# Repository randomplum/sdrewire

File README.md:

# SDReWire

Modern SD card muxer - allows to mux a SD card between an on-board USB SD card
reader and the device SDReWire is plugged into. This is useful for developing
and testing (embedded) systems which often require SD cards to boot from. It
allows to access the SD card on the target system as well as from the host
system connected via USB without having to touch the SD card.
 
Inspiried by the SDWire.

## Features

- USB-C connector for host system
- High speed signal muxer to mux SD signals
- SDXC/UHS capable design
- USB 3.1 Gen1 card reader (90MB/s+)
- FTDI for SD muxing and auxiliary port
- Auxiliary port featuring:
  - UART
  - 2 GPIO (1x output only)
  - 1.2V/1.8V/3.3V capable

Currenlty SDReWire is still in testing and development phase.

### Details

In case you wonder what exact components are used, here is the gist:

- USB 3.1 Gen1 card reader Genesys Logic GL3224
- TS3DDR4000ZBAR mux IC used for SD signals
- FTDI FT230XQ provides GPIO for mux as well as auxiliary UART and GPIO
- USB2422 USB 2.0 Hub to interface GL3224 and FTDI FT230XQ
  
Designed with KiCad.

## License

Licensed under the CERN-OHL-W (CERN Open Hardware Licence Version 2 - Weakly
Reciprocal, see LICENSE).

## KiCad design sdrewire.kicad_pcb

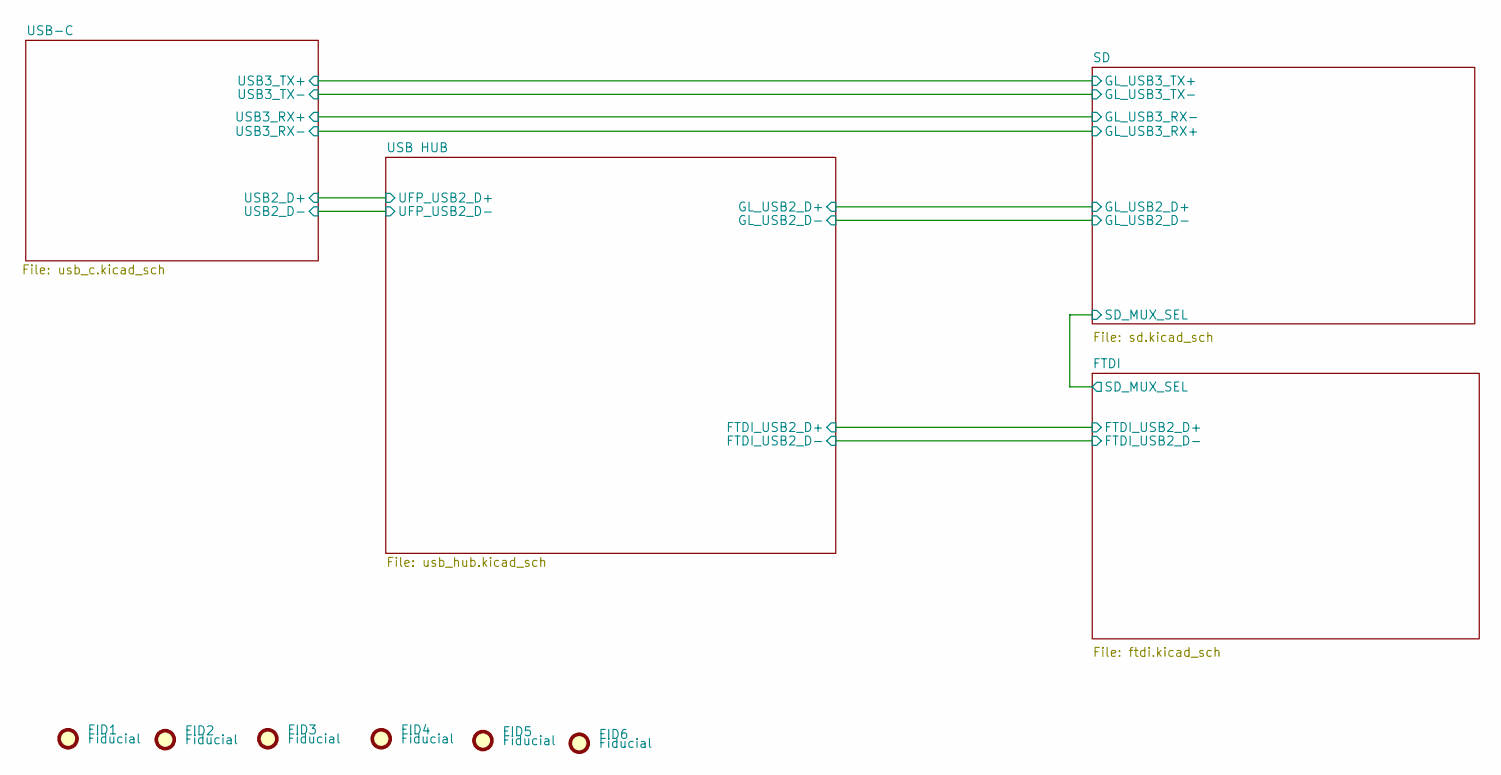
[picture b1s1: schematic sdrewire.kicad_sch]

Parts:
FID1, FID2, FID3, FID4, FID5, FID6: Fiducial; Fiducial_0.5mm_Mask1mm

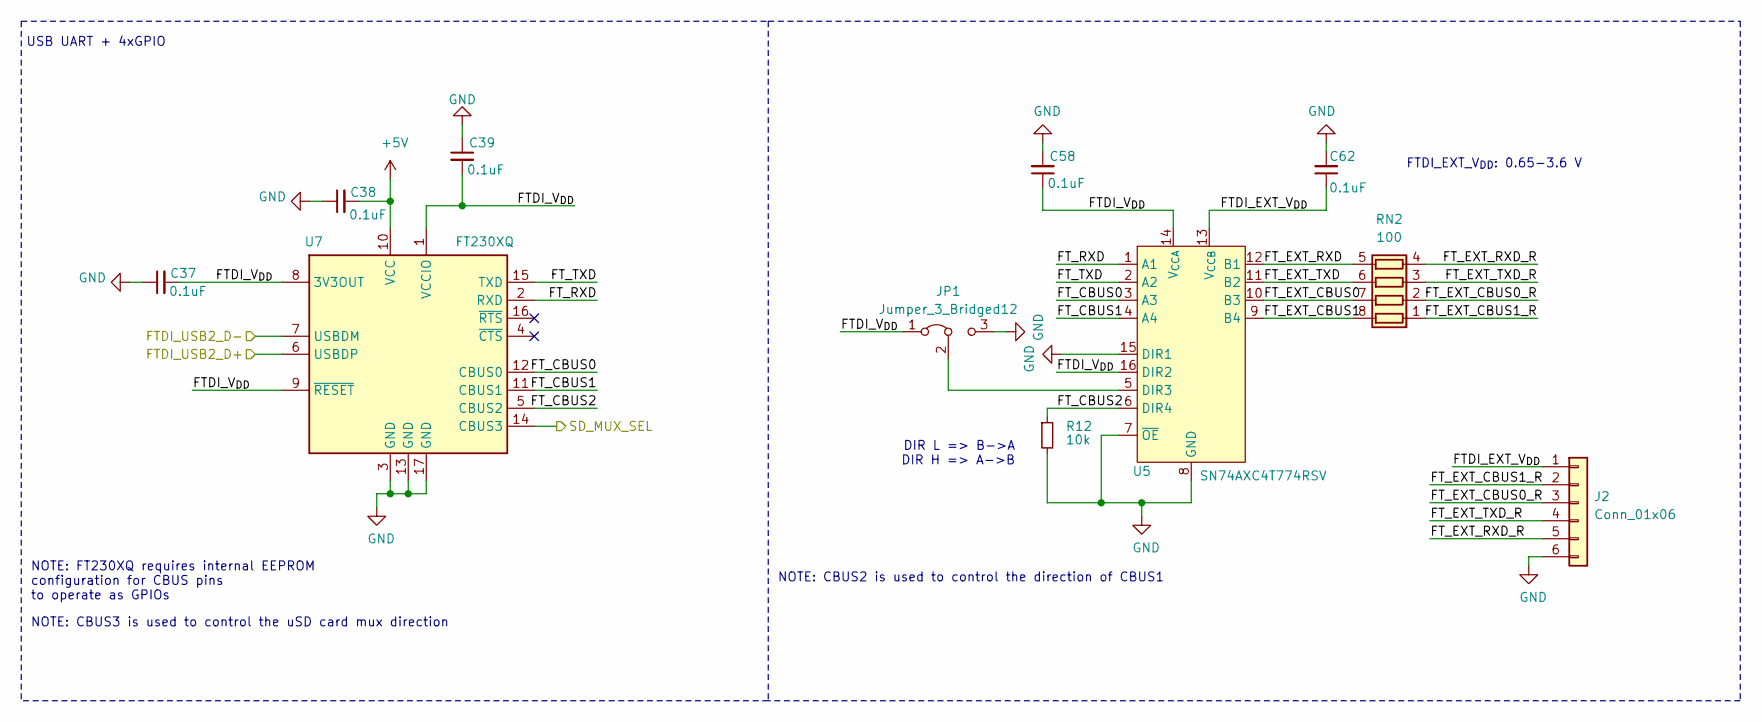
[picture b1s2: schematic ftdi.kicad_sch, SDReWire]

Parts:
C37, C38, C39, C58, C62: 0.1uF; C_0402_1005Metric
J2: Conn_01x06; JST_SH_SM06B-SRSS-TB_1x06-1MP_P1.00mm_Horizontal
JP1: Jumper_3_Bridged12; SolderJumper-3_P1.3mm_Bridged12_RoundedPad1.0x1.5mm_NumberL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
R12: 10k; R_0402_1005Metric
RN2: 100; R_Array_Convex_4x0402
U5: SN74AXC4T774RSV; QFN-16_1.8x2.6_Pitch0.4mm
U7: FT230XQ; QFN-16-1EP_4x4mm_P0.65mm_EP2.1x2.1mm

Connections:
+5V: C38.2, U7.10 (VCC); also elsewhere on the board
/FTDI/FTDI_EXT_V_{DD}: C62.1, J2.1, U5.13 (V_{CCB})
/FTDI/FTDI_USB2_D+: U7.6 (USBDP); also elsewhere on the board
/FTDI/FTDI_USB2_D-: U7.7 (USBDM); also elsewhere on the board
/FTDI/FTDI_V_{DD}: C37.2, C39.2, C58.1, JP1.1 (A), U5.14 (V_{CCA}), U5.16 (DIR2), U7.1 (VCCIO), U7.8 (3V3OUT), U7.9 (~RESET)
/FTDI/FT_CBUS0: U5.3 (A3), U7.12 (CBUS0)
/FTDI/FT_CBUS1: U5.4 (A4), U7.11 (CBUS1)
/FTDI/FT_CBUS2: R12.1, U5.6 (DIR4), U7.5 (CBUS2)
/FTDI/FT_EXT_CBUS0: RN2.7 (R2.2), U5.10 (B3)
/FTDI/FT_EXT_CBUS0_R: J2.3, RN2.2 (R2.1)
/FTDI/FT_EXT_CBUS1: RN2.8 (R1.2), U5.9 (B4)
/FTDI/FT_EXT_CBUS1_R: J2.2, RN2.1 (R1.1)
/FTDI/FT_EXT_RXD: RN2.5 (R4.2), U5.12 (B1)
/FTDI/FT_EXT_RXD_R: J2.5, RN2.4 (R4.1)
/FTDI/FT_EXT_TXD: RN2.6 (R3.2), U5.11 (B2)
/FTDI/FT_EXT_TXD_R: J2.4, RN2.3 (R3.1)
/FTDI/FT_RXD: U5.1 (A1), U7.2 (RXD)
/FTDI/FT_TXD: U5.2 (A2), U7.15 (TXD)
/FTDI/SD_MUX_SEL: U7.14 (CBUS3); also elsewhere on the board
GND: C37.1, C38.1, C39.1, C58.2, C62.2, J2.6, JP1.3 (B), R12.2, U5.7 (~OE), U5.8 (GND), U5.15 (DIR1), U7.3 (GND), U7.13 (GND), U7.17 (GND); also elsewhere on the board
unnamed: JP1.2 (C), U5.5 (DIR3)

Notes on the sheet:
USB UART + 4xGPIO
NOTE: FT230XQ requires internal EEPROM configuration for CBUS pins to operate as GPIOs
NOTE: CBUS3 is used to control the uSD card mux direction
NOTE: CBUS2 is used to control the direction of CBUS1
DIR L => B->A DIR H => A->B
FTDI_EXT_V_{DD}: 0.65-3.6 V

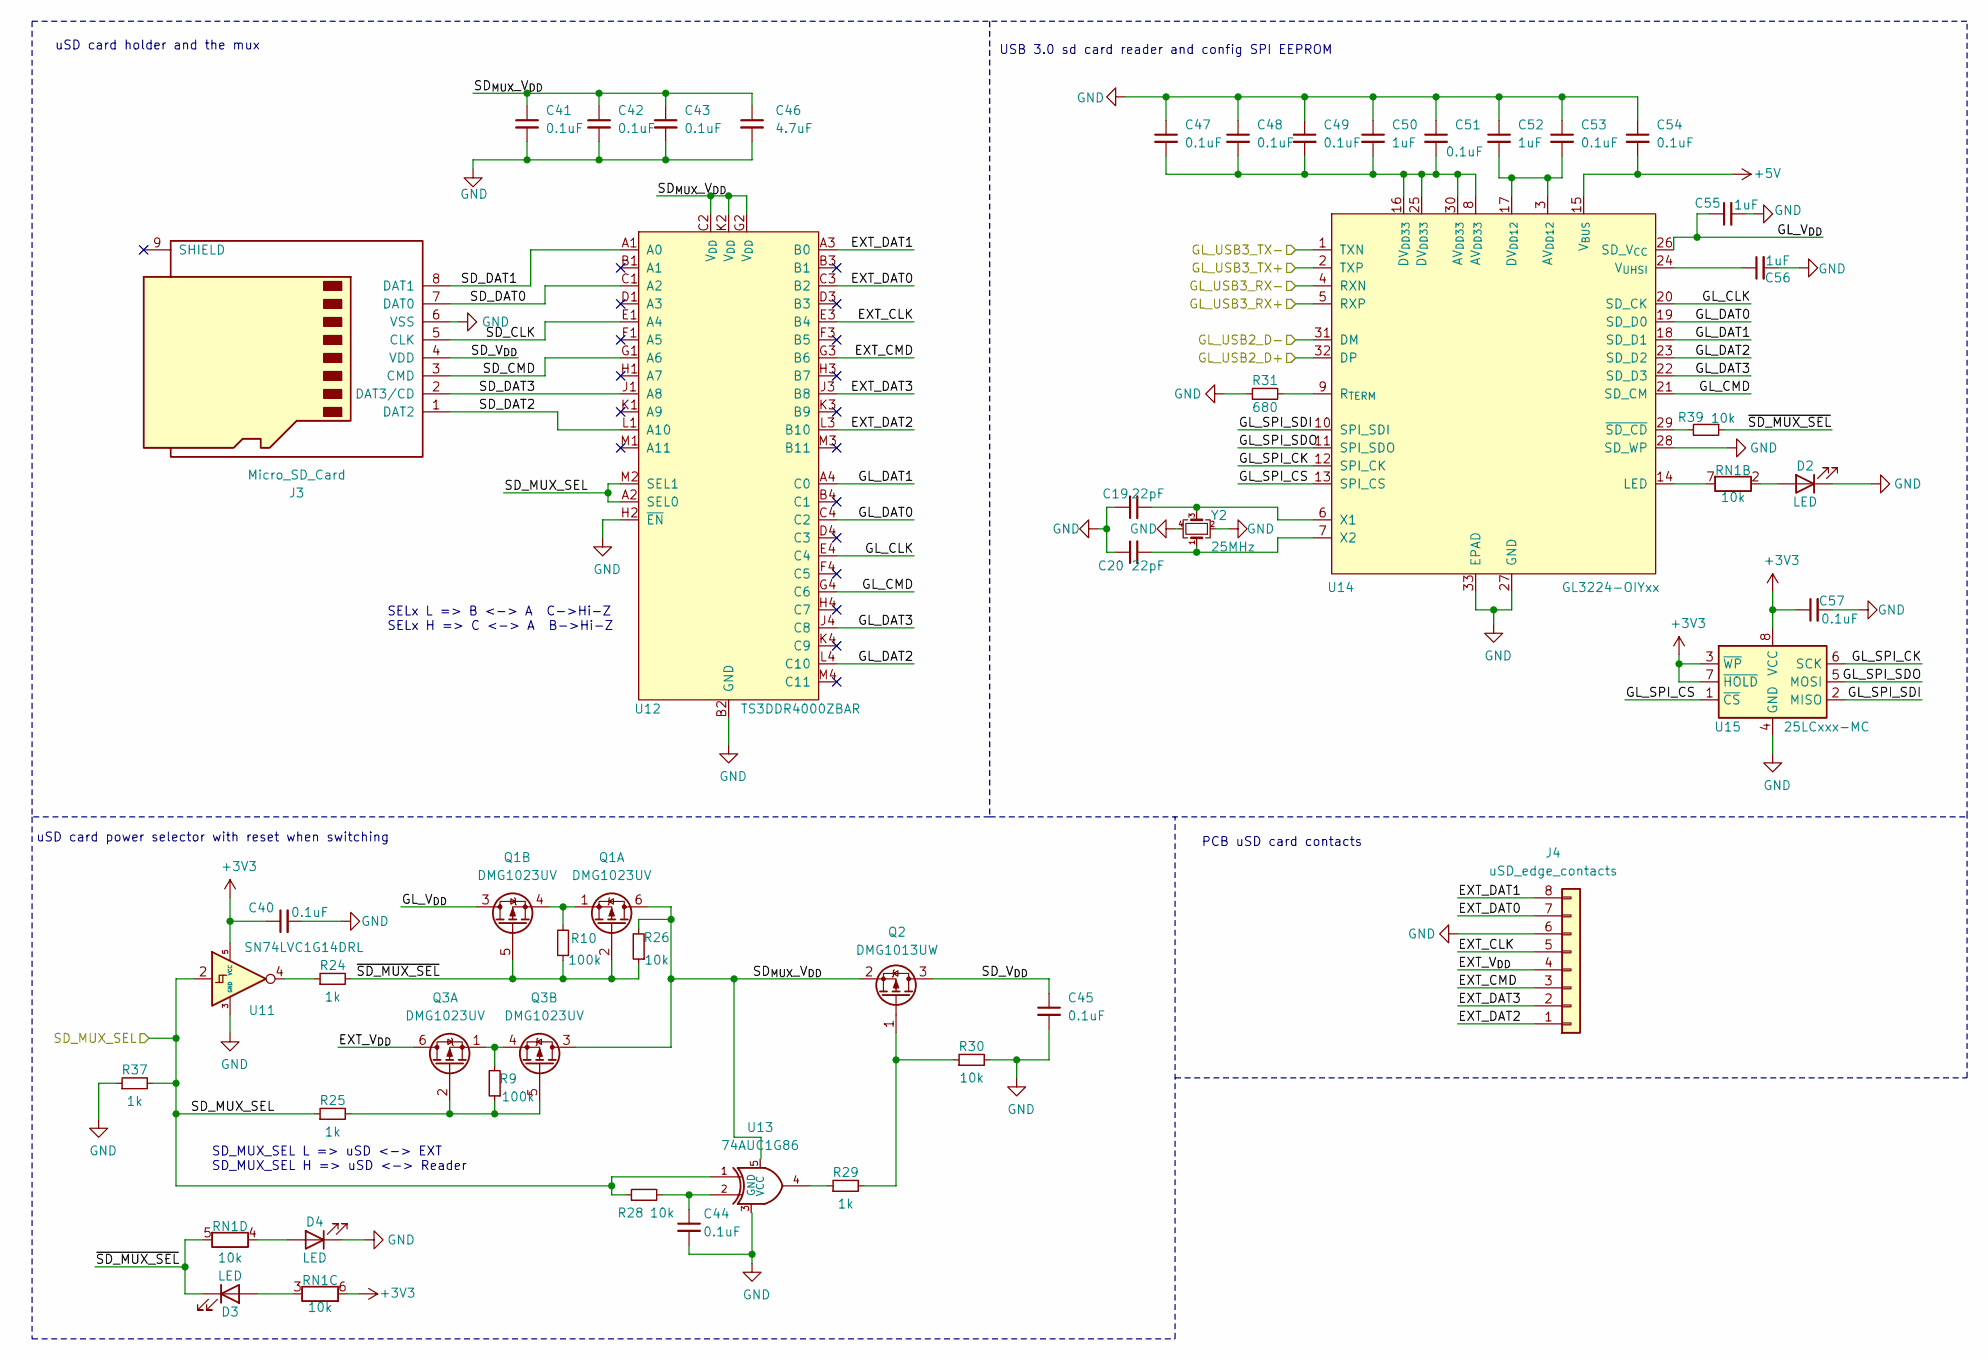
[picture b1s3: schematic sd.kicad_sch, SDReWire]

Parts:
C19, C20: 22pF; C_0402_1005Metric
C40, C41, C42, C43, C44, C45, C47, C48, C49, C51, C53, C54, C57: 0.1uF; C_0402_1005Metric
C46: 4.7uF; C_0402_1005Metric
C50, C52, C55, C56: 1uF; C_0402_1005Metric
D2, D3, D4: LED; LED_0402_1005Metric
J3: Micro_SD_Card; microSD_HC_Wuerth_693072010801
J4: uSD_edge_contacts; uSD_PCB
Q1, Q3: DMG1023UV; SOT-563
Q2: DMG1013UW; SOT-323_SC-70
R9, R10: 100k; R_0402_1005Metric
R24, R25, R29, R37: 1k; R_0402_1005Metric
R26, R28, R30, R39: 10k; R_0402_1005Metric
R31: 680; R_0402_1005Metric
RN1: 10k; R_Array_Convex_4x0402
U11: SN74LVC1G14DRL; SOT-553
U12: TS3DDR4000ZBAR; Texas_NFBGA-48_3.1x8.1mm_Layout4x12_P0.65mm
U13: 74AUC1G86; SOT-353_SC-70-5
U14: GL3224-OIYxx; QFN-32-1EP_5x5mm_P0.5mm_EP3.1x3.1mm
U15: 25LCxxx-MC; DFN-8-1EP_3x2mm_P0.5mm_EP1.75x1.45mm
Y2: 25MHz; Oscillator_SMD_Abracon_ASCO-4Pin_1.6x1.2mm

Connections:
+3V3: C40.1, C57.1, RN1.6 (R3.2), U11.5 (VCC), U15.3 (~WP), U15.7 (~HOLD), U15.8 (VCC); also elsewhere on the board
+5V: C54.2, U14.15 (V_{BUS}); also elsewhere on the board
/FTDI/SD_MUX_SEL: R25.1, R28.1, R37.2, U11.2, U12.A2 (SEL0), U12.M2 (SEL1), U13.1; also elsewhere on the board
/SD/EXT_CLK: J4.5, U12.E3 (B4)
/SD/EXT_CMD: J4.3, U12.G3 (B6)
/SD/EXT_DAT0: J4.7, U12.C3 (B2)
/SD/EXT_DAT1: J4.8, U12.A3 (B0)
/SD/EXT_DAT2: J4.1, U12.L3 (B10)
/SD/EXT_DAT3: J4.2, U12.J3 (B8)
/SD/EXT_V_{DD}: J4.4, Q3.6 (D)
/SD/GL_CLK: U12.E4 (C4), U14.20 (SD_CK)
/SD/GL_CMD: U12.G4 (C6), U14.21 (SD_CM)
/SD/GL_DAT0: U12.C4 (C2), U14.19 (SD_D0)
/SD/GL_DAT1: U12.A4 (C0), U14.18 (SD_D1)
/SD/GL_DAT2: U12.L4 (C10), U14.23 (SD_D2)
/SD/GL_DAT3: U12.J4 (C8), U14.22 (SD_D3)
/SD/GL_SPI_CK: U14.12 (SPI_CK), U15.6 (SCK)
/SD/GL_SPI_CS: U14.13 (SPI_CS), U15.1 (~CS)
/SD/GL_SPI_SDI: U14.10 (SPI_SDI), U15.2 (MISO)
/SD/GL_SPI_SDO: U14.11 (SPI_SDO), U15.5 (MOSI)
/SD/GL_USB2_D+: U14.32 (DP); also elsewhere on the board
/SD/GL_USB2_D-: U14.31 (DM); also elsewhere on the board
/SD/GL_USB3_RX+: U14.5 (RXP); also elsewhere on the board
/SD/GL_USB3_RX-: U14.4 (RXN); also elsewhere on the board
/SD/GL_USB3_TX+: U14.2 (TXP); also elsewhere on the board
/SD/GL_USB3_TX-: U14.1 (TXN); also elsewhere on the board
/SD/GL_V_{DD}: C55.1, Q1.3 (D), U14.26 (SD_V_{CC})
/SD/SD_CLK: J3.5 (CLK), U12.E1 (A4)
/SD/SD_CMD: J3.3 (CMD), U12.G1 (A6)
/SD/SD_DAT0: J3.7 (DAT0), U12.C1 (A2)
/SD/SD_DAT1: J3.8 (DAT1), U12.A1 (A0)
/SD/SD_DAT2: J3.1 (DAT2), U12.L1 (A10)
/SD/SD_DAT3: J3.2 (DAT3/CD), U12.J1 (A8)
/SD/SD_V_{DD}: C45.1, J3.4 (VDD), Q2.3 (D)
/SD/SD_{MUX}_V_{DD}: C41.1, C42.1, C43.1, C46.1, Q1.6 (D), Q2.2 (S), Q3.3 (D), R26.2, U12.C2 (V_{DD}), U12.G2 (V_{DD}), U12.K2 (V_{DD})
/SD/~SD_MUX_SEL: D3.1 (K), Q1.2 (G), Q1.5 (G), R10.1, R24.2, R26.1, R39.1, RN1.5 (R4.2)
GND: C19.1, C20.1, C40.2, C41.2, C42.2, C43.2, C44.2, C45.2, C46.2, C47.1, C48.1, C49.1, C50.1, C51.1, C52.1, C53.1, C54.1, C55.2, C56.2, C57.2, D2.1 (K), D4.1 (K), J3.6 (VSS), J4.6, R30.2, R31.1, R37.1, U11.3 (GND), U12.B2 (GND), U12.D2 (GND), U12.E2 (GND), U12.F2 (GND), U12.H2 (~EN), U12.J2 (GND), U12.L2 (GND), U14.27 (GND), U14.28 (SD_WP), U14.33 (EPAD), U15.4 (GND), U15.9 (GND), Y2.2, Y2.4; also elsewhere on the board
unnamed: C19.2, U14.6 (X1), Y2.3
unnamed: C20.2, U14.7 (X2), Y2.1
unnamed: C44.1, R28.2, U13.2
unnamed: C47.2, C48.2, C49.2, C50.2, C51.2, U14.8 (AV_{DD33}), U14.16 (DV_{DD33}), U14.25 (DV_{DD33}), U14.30 (AV_{DD33})
unnamed: C52.2, C53.2, U14.3 (AV_{DD12}), U14.17 (DV_{DD12})
unnamed: C56.1, U14.24 (V_{UHSI})
unnamed: D2.2 (A), RN1.2 (R2.1)
unnamed: D3.2 (A), RN1.3 (R3.1)
unnamed: D4.2 (A), RN1.4 (R4.1)
unnamed: Q1.1 (S), Q1.4 (S), R10.2
unnamed: Q2.1 (G), R29.2, R30.1
unnamed: Q3.1 (S), Q3.4 (S), R9.2
unnamed: Q3.2 (G), Q3.5 (G), R9.1, R25.2
unnamed: R24.1, U11.4
unnamed: R29.1, U13.4
unnamed: R31.2, U14.9 (R_{TERM})
unnamed: R39.2, U14.29 (~SD_CD)
unnamed: RN1.7 (R2.2), U14.14 (LED)

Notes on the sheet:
uSD card power selector with reset when switching
SD_MUX_SEL L => uSD <-> EXT SD_MUX_SEL H => uSD <-> Reader
uSD card holder and the mux
SELx L => B <-> A C->Hi-Z SELx H => C <-> A B->Hi-Z
USB 3.0 sd card reader and config SPI EEPROM
PCB uSD card contacts

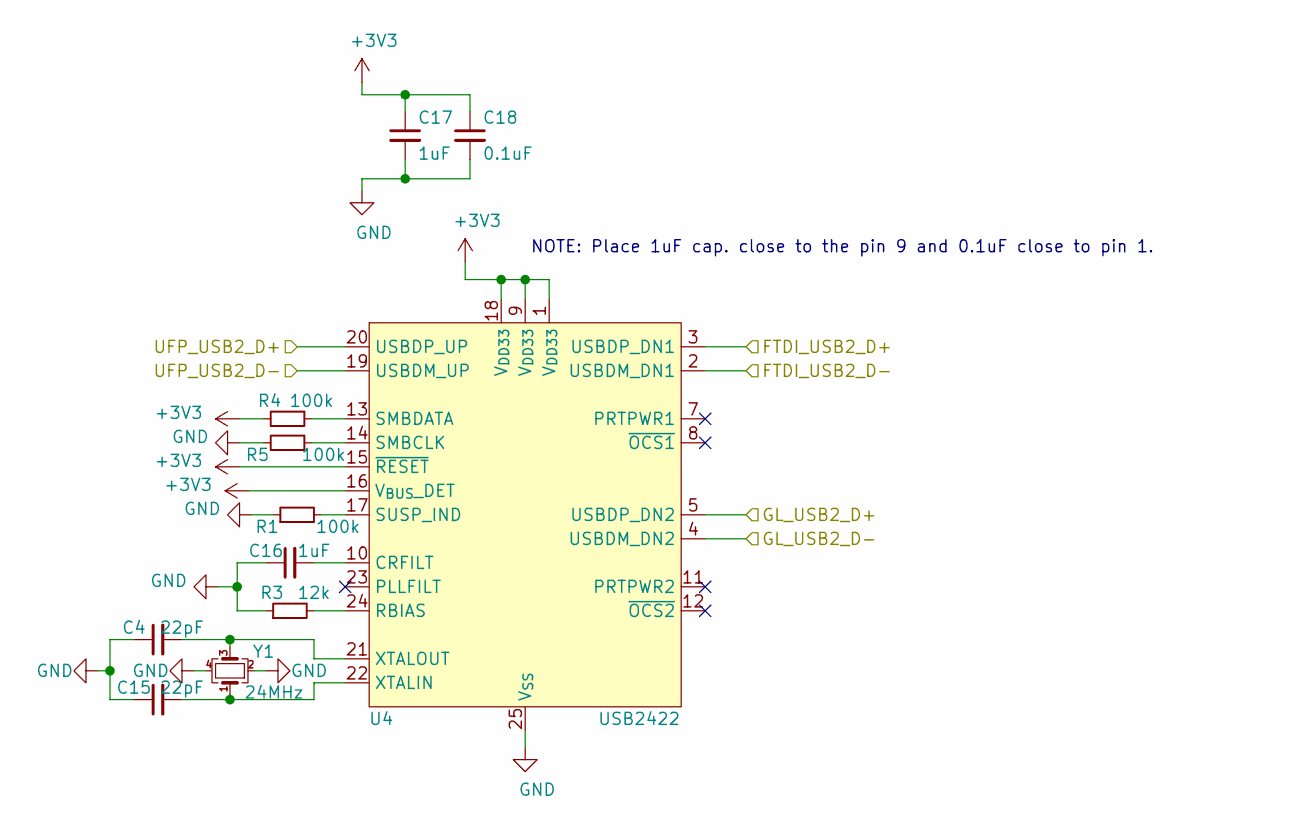
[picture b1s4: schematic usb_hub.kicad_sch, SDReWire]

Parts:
C4, C15: 22pF; C_0402_1005Metric
C16, C17: 1uF; C_0402_1005Metric
C18: 0.1uF; C_0402_1005Metric
R1, R4, R5: 100k; R_0402_1005Metric
R3: 12k; R_0402_1005Metric
U4: USB2422; QFN-24-1EP_4x4mm_P0.5mm_EP2.6x2.6mm
Y1: 24MHz; Oscillator_SMD_Abracon_ASCO-4Pin_1.6x1.2mm

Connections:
+3V3: C17.1, C18.1, R4.1, U4.1 (V_{DD33}), U4.9 (V_{DD33}), U4.15 (~RESET), U4.16 (V_{BUS}_DET), U4.18 (V_{DD33}); also elsewhere on the board
/FTDI/FTDI_USB2_D+: U4.3 (USBDP_DN1); also elsewhere on the board
/FTDI/FTDI_USB2_D-: U4.2 (USBDM_DN1); also elsewhere on the board
/SD/GL_USB2_D+: U4.5 (USBDP_DN2); also elsewhere on the board
/SD/GL_USB2_D-: U4.4 (USBDM_DN2); also elsewhere on the board
/USB HUB/UFP_USB2_D+: U4.20 (USBDP_UP); also elsewhere on the board
/USB HUB/UFP_USB2_D-: U4.19 (USBDM_UP); also elsewhere on the board
GND: C4.1, C15.1, C16.1, C17.2, C18.2, R1.1, R3.1, R5.1, U4.25 (V_{SS}), Y1.2, Y1.4; also elsewhere on the board
unnamed: C4.2, U4.21 (XTALOUT), Y1.3
unnamed: C15.2, U4.22 (XTALIN), Y1.1
unnamed: C16.2, U4.10 (CRFILT)
unnamed: R3.2, U4.24 (RBIAS)
unnamed: R4.2, U4.13 (SMBDATA)
unnamed: R5.2, U4.14 (SMBCLK)
unnamed: R1.2, U4.17 (SUSP_IND)

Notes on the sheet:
NOTE: Place 1uF cap. close to the pin 9 and 0.1uF close to pin 1.

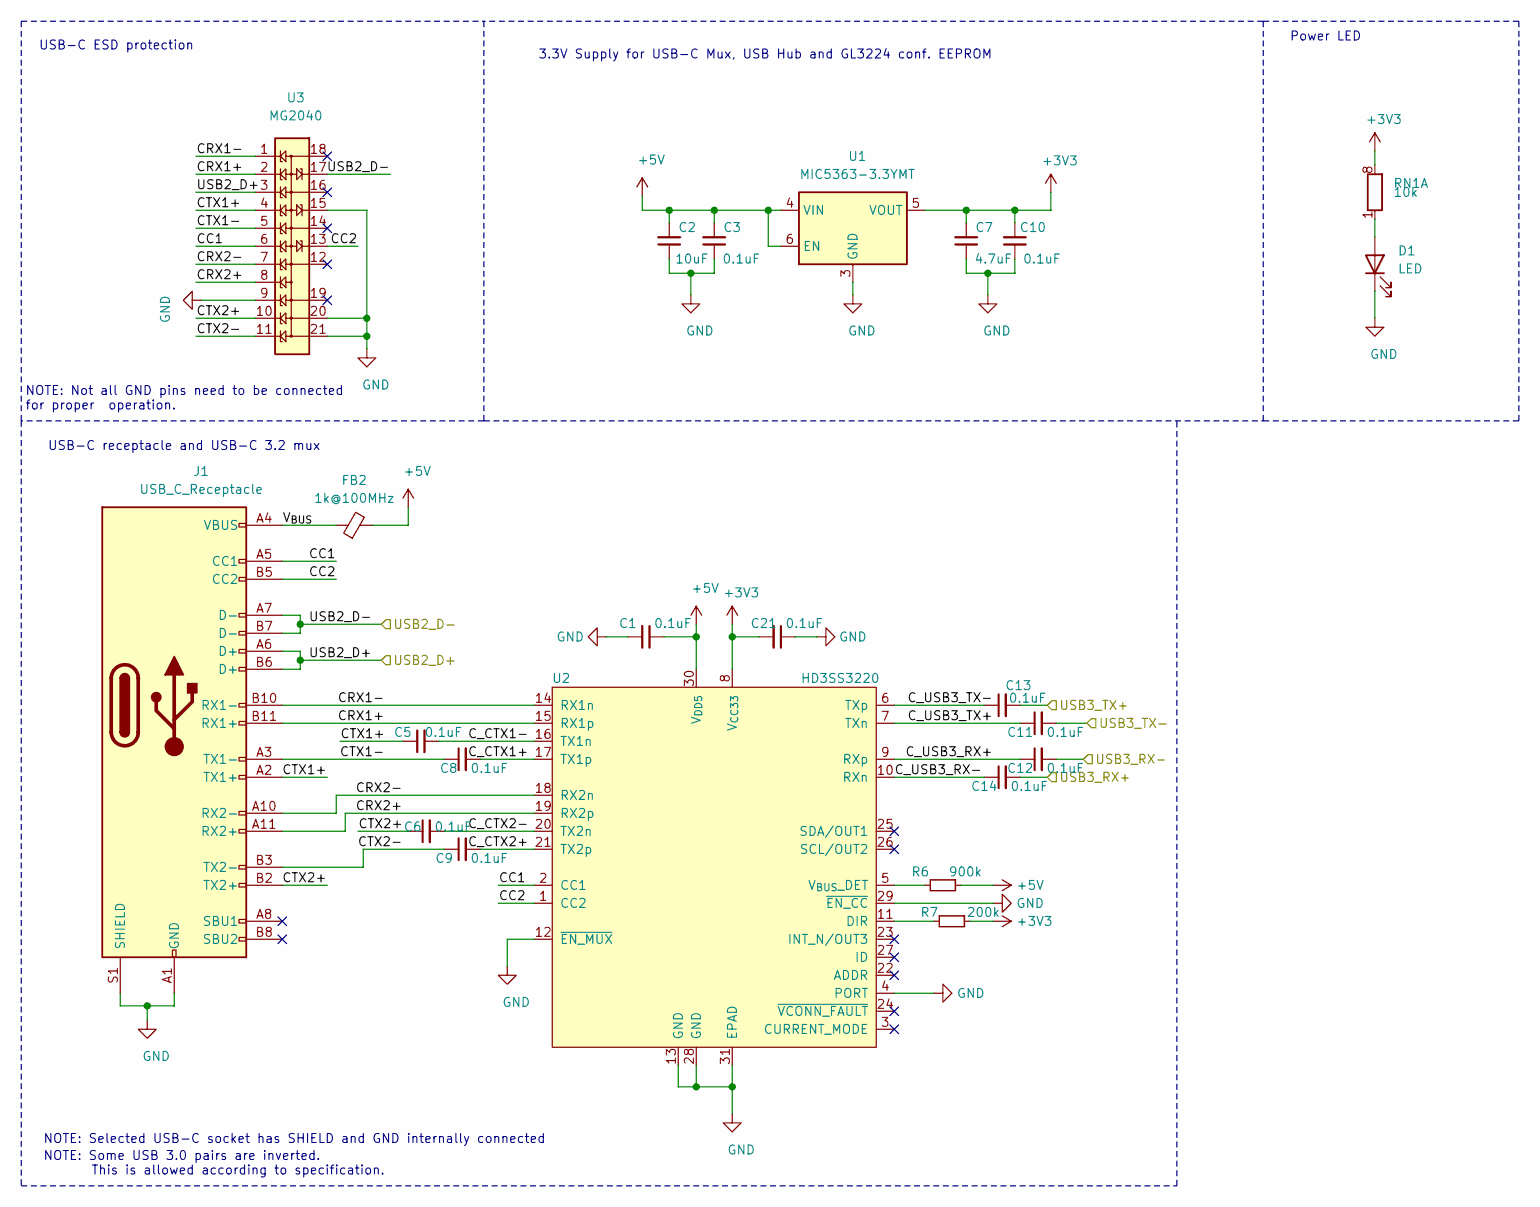
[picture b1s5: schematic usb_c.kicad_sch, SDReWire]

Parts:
C1, C3, C5, C6, C8, C9, C10, C11, C12, C13, C14, C21: 0.1uF; C_0402_1005Metric
C2: 10uF; C_0402_1005Metric
C7: 4.7uF; C_0402_1005Metric
D1: LED; LED_0402_1005Metric
FB2: 1k@100MHz; R_0603_1608Metric
J1: USB_C_Receptacle; USB_C_Receptacle_Molex_1054500101
R6: 900k; R_0402_1005Metric
R7: 200k; R_0402_1005Metric
RN1: 10k; R_Array_Convex_4x0402
U1: MIC5363-3.3YMT; DFN-6-1EP_1.2x1.2mm_P0.4mm_EP0.3x0.94mm_PullBack
U2: HD3SS3220; WQFP-30-1EP_4.6x2.6mm_P0.4mm_EP3.2x1.2mm
U3: MG2040; UDFN-18-3EP_5.5x1.5mm_P0.5mm_EP0.5x0.5mm

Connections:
+3V3: C7.2, C10.2, C21.2, R7.1, RN1.8 (R1.2), U1.5 (VOUT), U2.8 (V_{CC33}); also elsewhere on the board
+5V: C1.1, C2.2, C3.2, FB2.2, R6.1, U1.4 (VIN), U1.6 (EN), U2.30 (V_{DD5}); also elsewhere on the board
/SD/GL_USB3_RX+: C12.2; also elsewhere on the board
/SD/GL_USB3_RX-: C14.2; also elsewhere on the board
/SD/GL_USB3_TX+: C13.2; also elsewhere on the board
/SD/GL_USB3_TX-: C11.2; also elsewhere on the board
/USB HUB/UFP_USB2_D+: J1.A6 (D+), J1.B6 (D+), U3.3; also elsewhere on the board
/USB HUB/UFP_USB2_D-: J1.A7 (D-), J1.B7 (D-), U3.17; also elsewhere on the board
/USB-C/CC1: J1.A5 (CC1), U2.2 (CC1), U3.6
/USB-C/CC2: J1.B5 (CC2), U2.1 (CC2), U3.13
/USB-C/CRX1+: J1.B11 (RX1+), U2.15 (RX1p), U3.2
/USB-C/CRX1-: J1.B10 (RX1-), U2.14 (RX1n), U3.1
/USB-C/CRX2+: J1.A11 (RX2+), U2.19 (RX2p), U3.8
/USB-C/CRX2-: J1.A10 (RX2-), U2.18 (RX2n), U3.7
/USB-C/CTX1+: C5.1, J1.A2 (TX1+), U3.4
/USB-C/CTX1-: C8.1, J1.A3 (TX1-), U3.5
/USB-C/CTX2+: C6.1, J1.B2 (TX2+), U3.10
/USB-C/CTX2-: C9.1, J1.B3 (TX2-), U3.11
/USB-C/C_CTX1+: C8.2, U2.17 (TX1p)
/USB-C/C_CTX1-: C5.2, U2.16 (TX1n)
/USB-C/C_CTX2+: C9.2, U2.21 (TX2p)
/USB-C/C_CTX2-: C6.2, U2.20 (TX2n)
/USB-C/C_USB3_RX+: C12.1, U2.9 (RXp)
/USB-C/C_USB3_RX-: C14.1, U2.10 (RXn)
/USB-C/C_USB3_TX+: C11.1, U2.7 (TXn)
/USB-C/C_USB3_TX-: C13.1, U2.6 (TXp)
/USB-C/V_{BUS}: FB2.1, J1.A4 (VBUS), J1.A9 (VBUS), J1.B4 (VBUS), J1.B9 (VBUS)
GND: C1.2, C2.1, C3.1, C7.1, C10.1, C21.1, D1.1 (K), J1.A1 (GND), J1.A12 (GND), J1.B1 (GND), J1.B12 (GND), J1.S1 (SHIELD), U1.3 (GND), U1.7 (ePad), U2.4 (PORT), U2.12 (~EN_MUX), U2.13 (GND), U2.28 (GND), U2.29 (~EN_CC), U2.31 (EPAD), U3.9, U3.15, U3.20, U3.21; also elsewhere on the board
unnamed: D1.2 (A), RN1.1 (R1.1)
unnamed: R6.2, U2.5 (V_{BUS}_DET)
unnamed: R7.2, U2.11 (DIR)

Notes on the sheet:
NOTE: Not all GND pins need to be connected for proper operation.
USB-C ESD protection
NOTE: Selected USB-C socket has SHIELD and GND internally connected
NOTE: Some USB 3.0 pairs are inverted. This is allowed according to specification.
USB-C receptacle and USB-C 3.2 mux
3.3V Supply for USB-C Mux, USB Hub and GL3224 conf. EEPROM
Power LED

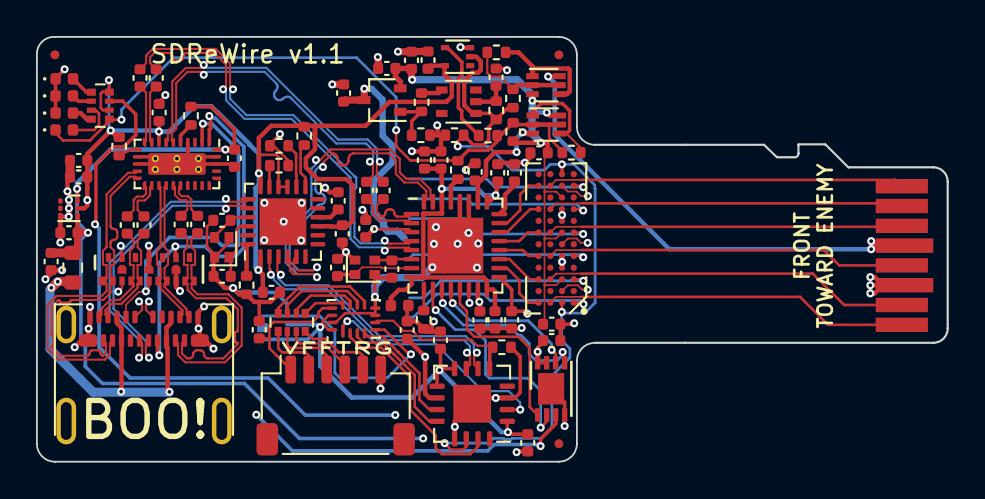
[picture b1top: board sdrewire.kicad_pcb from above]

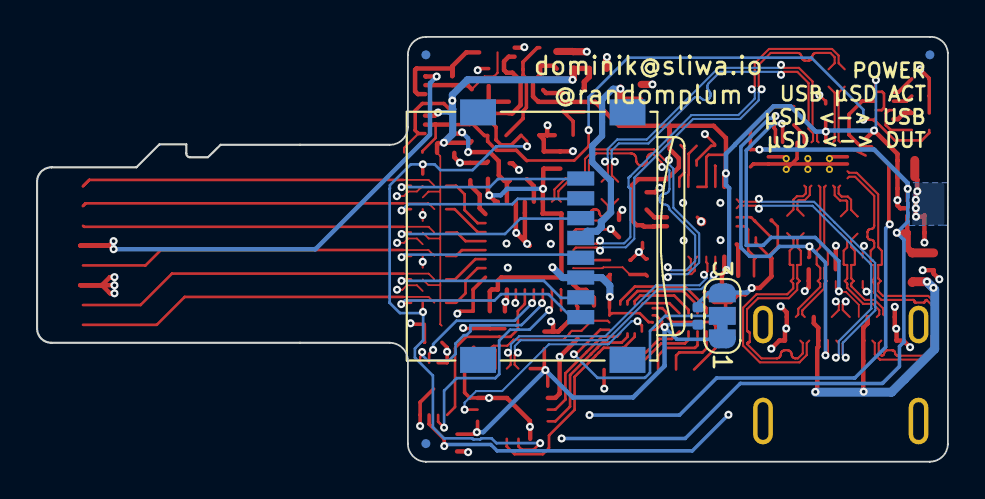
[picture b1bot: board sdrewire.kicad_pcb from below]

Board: 4 copper layers, 50.6 x 23.6 mm, 96 parts (6 on the bottom side), 104 nets.

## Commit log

2020-11-23 SDReWire: v1 schematics
2020-11-23 sd.kicad_sch: fix power select PMOSes
    Back-to-back configuration should use transitors from the same package.
2020-11-23 SDReWire: Footprint assigment
2020-11-23 SDReWire: rename FTDI_GPIO to SD_MUX_SEL and fix assigment
    Resistor array had a wrong footprint
2020-11-23 SDReWire: fix assigments
    modify few components footprint assigments
2020-11-23 sdrewire.kicad_pcb: initial PCB file
2020-11-23 SDReWire: add configurable link for gpio dir
2020-11-23 sd.kicad_sch: improve SD_MUX_SEL net readability
2020-11-23 SDReWire: fix MIC5363 symbol
2020-11-23 usb_c.kicad_sch: swap usb 3 pairs at MG2040
2020-11-24 Fix direction of hierarchical label SD_MUX_SEL
2020-11-24 Add README.md and LICENSE
    Put the project under the CERN-OHL-W license. This is a weakly
    reciprocal license, for the example above, if you release your part
    of the design under CERN-OHL-W, somebody who distributes a bitstream
    which includes your part does not need to distribute the rest of the
    design files as well.
2020-11-24 Update README.md
    Added 1.2V ftdi IO voltage option and few fixups.
2020-11-29 sdrewire: pcb v1
    Some itra-pair inversions for easier routing.
    Fixed crystal pinouts
    sd power p-fet changed for smaller package
2020-11-30 SDReWire: v1.0 production data
2020-11-30 README.md: add render image
2020-12-02 SDReWire: fix back-to-back transistors circuit
2021-02-10 Changes:
    -fix led order
    -fix transistor routing
    -modify usb hub strapping and fix crystal footprint
    -remove copper under sd pads
    -routing cleanup
    -change revision to 1.1
2021-02-11 PCB: traces cleanup
